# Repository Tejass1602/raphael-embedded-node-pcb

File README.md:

# Raphael Embedded Node PCB

Custom PCB for the embedded hardware node of Raphael, a local AI engineering copilot.

## Overview

The embedded node is designed to support audio acquisition, lightweight event detection, and communication with a host computer over USB.

## Hardware

- MCU: ESP32-S3-WROOM-1-N8R8
- USB: USB Type-C
- Voltage regulator: AP2112K-3.3
- USB ESD protection: USBLC6-2SC6
- Audio interface: External I2S microphone connector

## I2S Interface

| Signal | ESP32-S3 GPIO |
|---|---|
| BCLK | GPIO4 |
| WS / LRCLK | GPIO5 |
| SD | GPIO6 |
| Power | 3.3 V |
| Ground | GND |

## Repository Structure

- KiCad project, schematic, and PCB layout files: Native hardware design.
- docs/evidence/: Genuine screenshots and validation records.
- manufacturing/: Fabrication outputs when generated.

## Development Status

PCB design and layout are in progress.

Design-rule checks, electrical validation, and mechanical verification must be completed before declaring the board fabrication-ready.

## Tools

- KiCad
- Git
- GitHub

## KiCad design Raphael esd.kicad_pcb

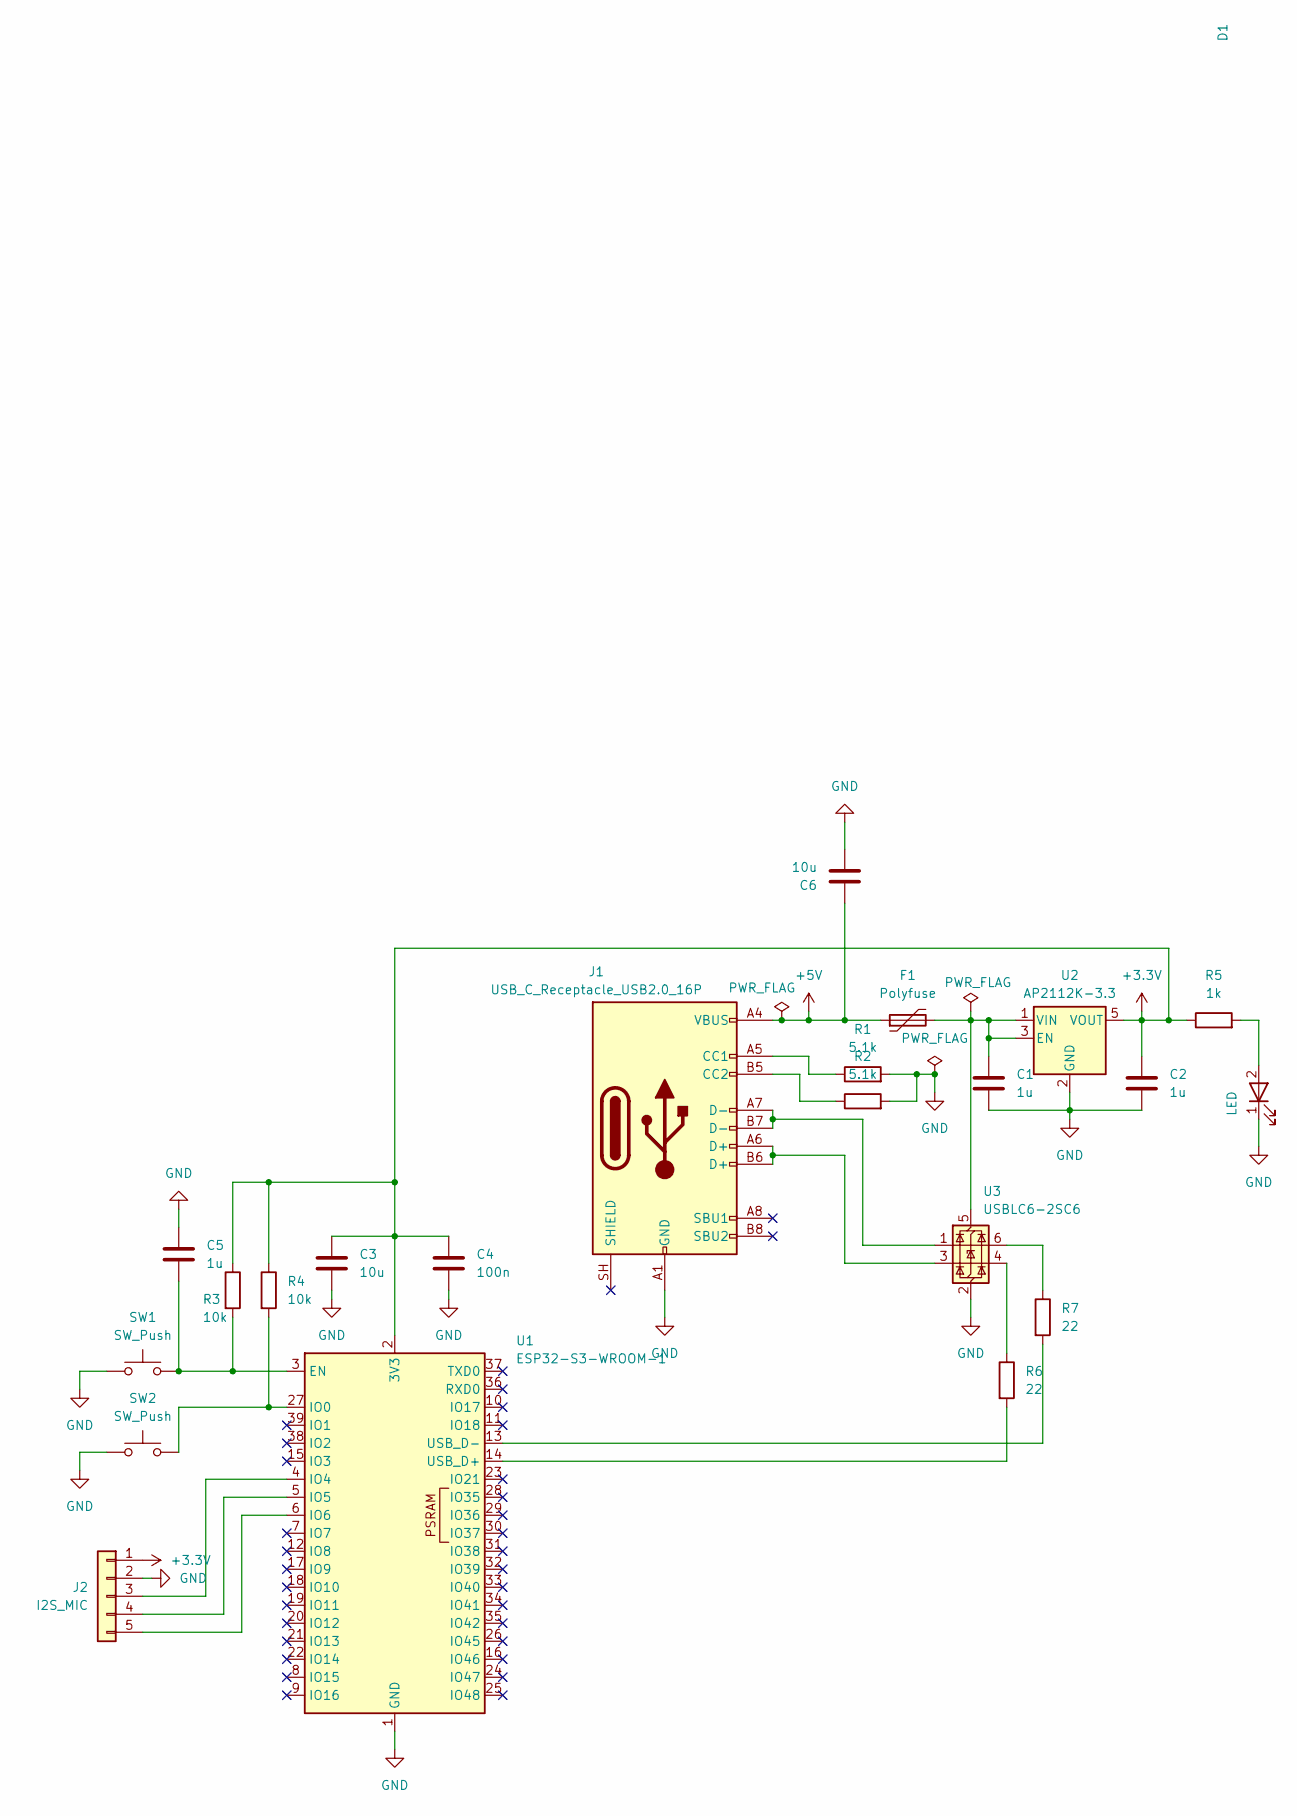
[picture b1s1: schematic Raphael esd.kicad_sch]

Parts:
C1, C2, C5: 1u; C_0805_2012Metric
C3, C6: 10u; C_0805_2012Metric
C4: 100n; C_0805_2012Metric
D1: LED; LED_0805_2012Metric
F1: Polyfuse; Fuse_1812_4532Metric
J1: USB_C_Receptacle_USB2.0_16P; USB_C_Receptacle_HRO_TYPE-C-31-M-12
J2: I2S_MIC; PinHeader_1x05_P2.54mm_Vertical
R1, R2: 5.1k; R_0805_2012Metric
R3, R4: 10k; R_0805_2012Metric
R5: 1k; R_0805_2012Metric
R6, R7: 22; R_0805_2012Metric
SW1, SW2: SW_Push; SW_PUSH_6mm
U1: ESP32-S3-WROOM-1
U2: AP2112K-3.3; SOT-23-5
U3: USBLC6-2SC6; SOT-23-6

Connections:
+3.3V: C2.1, C3.1, C4.1, J2.1 (3V3), R3.1, R4.1, R5.1, U1.2 (3V3), U2.5 (VOUT)
+5V: C6.1, F1.1, J1.A4 (VBUS), J1.A9 (VBUS), J1.B4 (VBUS), J1.B9 (VBUS)
GND: C1.2, C2.2, C3.2, C4.2, C5.1, C6.2, D1.1 (K), J1.A1 (GND), J1.A12 (GND), J1.B1 (GND), J1.B12 (GND), J2.2 (GND), R1.2, R2.2, SW1.1, SW2.1, U1.1 (GND), U1.40 (GND), U1.41 (GND), U2.2 (GND), U3.2 (GND)
unnamed: D1.2 (A), R5.2
unnamed: J1.A5 (CC1), R1.1
unnamed: J1.B5 (CC2), R2.1
unnamed: J1.A6 (D+), J1.B6 (D+), U3.3 (I/O2)
unnamed: J1.A7 (D-), J1.B7 (D-), U3.1 (I/O1)
unnamed: J2.3 (BCLK), U1.4 (IO4)
unnamed: J2.5 (SD), U1.6 (IO6)
unnamed: J2.4 (WS), U1.5 (IO5)
unnamed: R6.1, U3.4 (I/O2)
unnamed: R7.1, U3.6 (I/O1)
unnamed: C5.2, R3.2, SW1.2, U1.3 (EN)
unnamed: R4.2, SW2.2, U1.27 (IO0)
unnamed: R6.2, U1.14 (USB_D+)
unnamed: R7.2, U1.13 (USB_D-)
unnamed: C1.1, F1.2, U2.1 (VIN), U2.3 (EN), U3.5 (VBUS)

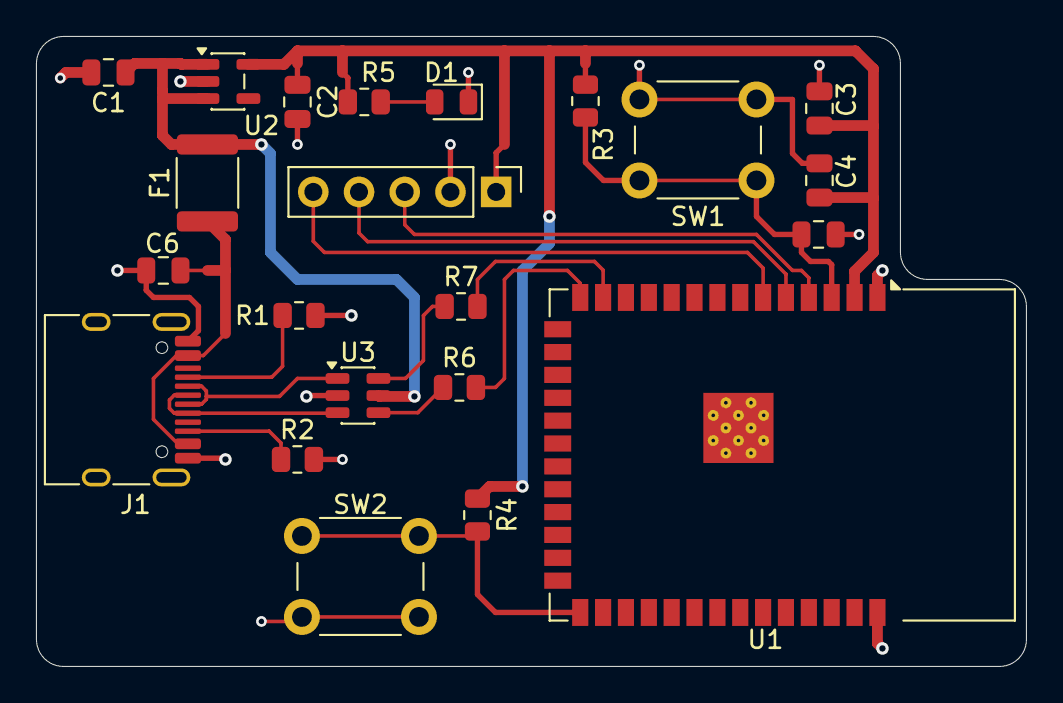
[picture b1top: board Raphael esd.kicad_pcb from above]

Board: 2 copper layers, 55.0 x 35.0 mm, 22 parts (0 on the bottom side), 18 nets.
